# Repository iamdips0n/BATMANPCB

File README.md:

# BATMANPCB
It is an supercool batman design on a PCB batarang, with a keychain hole. It is a cell battery powered with some cool LEDs.

## Schematic

## PCB

## Features
- cell battery powered
- cool LEDs
- keychain hole
- supercool batman design on a PCB batarang

## How to build
Just order the PCB & components, open up the KiCAD file and build it accordingly.

## BOM
- 1 battery holder
- 1 switch
- 6 resistor
- 6 LED

Made by `@iamdips0n1` on slack :D

Made as a part of http://solder.hackclub.com/!

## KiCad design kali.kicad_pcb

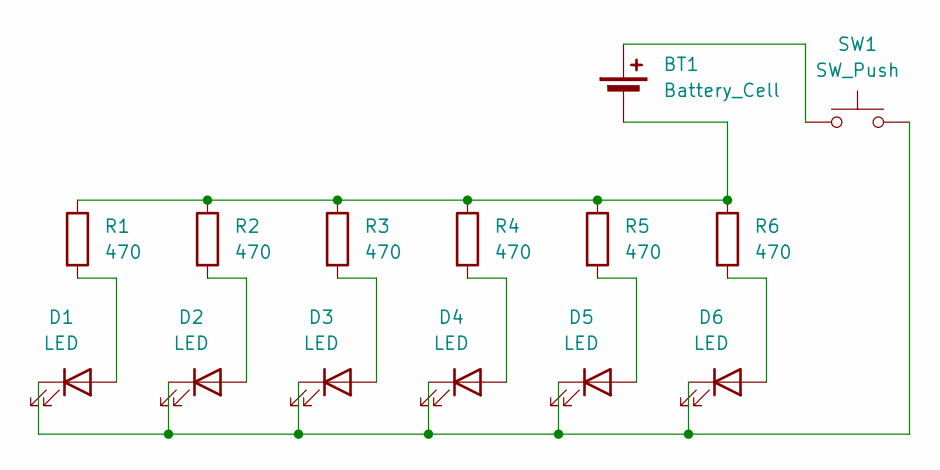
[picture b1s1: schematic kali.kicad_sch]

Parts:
BT1: Battery_Cell; BatteryHolder_Keystone_3034_1x20mm
D1, D2, D3, D4, D5, D6: LED; LED_D5.0mm
R1, R2, R3, R4, R5, R6: 470; R_Axial_DIN0207_L6.3mm_D2.5mm_P7.62mm_Horizontal
SW1: SW_Push; SW_PUSH_6mm

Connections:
unnamed: BT1.1 (+), SW1.1
unnamed: BT1.2 (-), R1.1, R2.1, R3.1, R4.1, R5.1, R6.1
unnamed: D1.2 (A), R1.2
unnamed: D1.1 (K), D2.1 (K), D3.1 (K), D4.1 (K), D5.1 (K), D6.1 (K), SW1.2
unnamed: D2.2 (A), R2.2
unnamed: D3.2 (A), R3.2
unnamed: D4.2 (A), R4.2
unnamed: D5.2 (A), R5.2
unnamed: D6.2 (A), R6.2

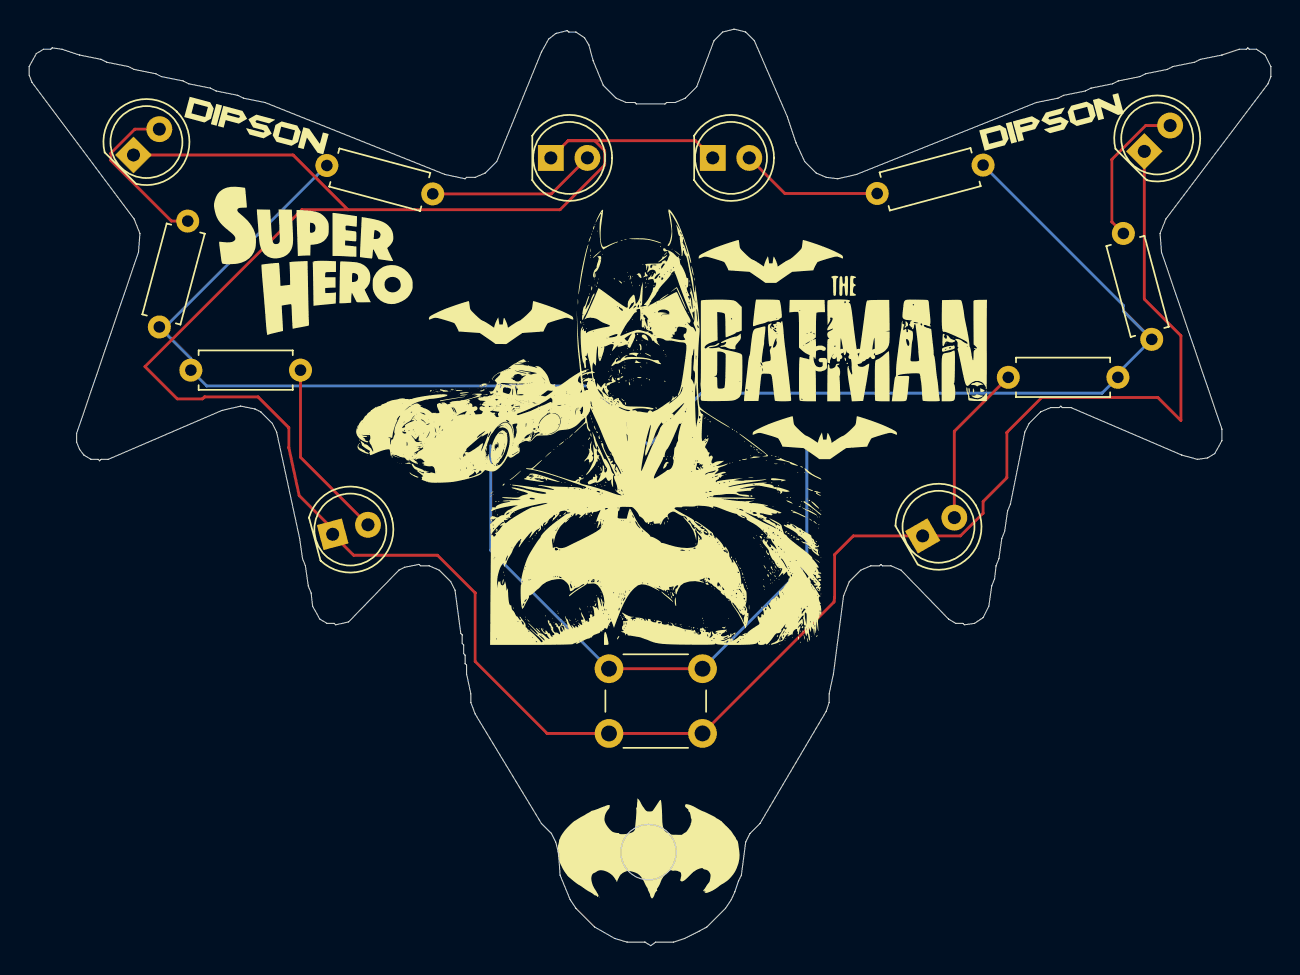
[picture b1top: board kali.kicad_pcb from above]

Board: 2 copper layers, 86.3 x 63.7 mm, 14 parts (1 on the bottom side), 9 nets.
